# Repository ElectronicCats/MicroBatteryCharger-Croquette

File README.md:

# Electronic Cats Croquette Micro Lipo/Lion Battery Charger

This little lipo charger is so small and easy to use you can keep it on your desk or mount it easily into any project! A 3.7V/4.2V lithium polymer or lithium ion rechargeable battery into the connectors. There are two LEDs - one red and one green. While charging, the red LED is lit. When the battery is fully charged and ready for use, the green LED turns on. Seriously, it could not get more easy.

For use with LiPoly/LiIon batteries only! Other batteries may have different voltage, chemistry, polarity or pinout. Lipo/Lipoly/LiIon Batteries not included, but we've got tons in the shop.

Charging is performed in three stages: first a preconditioning charge, then a constant-current fast charge and finally a constant-voltage trickle charge to keep the battery topped-up. The charge current is 100mA by default, so it will work with any size battery and USB port. If you want you can easily change it over to 500mA mode by soldering closed the jumper on the front, for when you'll only be charging batteries with 500mAh size or larger.

- 5V input
- For charging single Lithium Ion/Lithium Polymer 3.7/4.2v batteries (not for older 3.6/4.1v cells)
- 100mA charge current, adjustable to 500mA by soldering a jumper closed

### Maintainer

Electronic Cats invests time and resources providing this open source design, please support Electronic Cats and open-source hardware by purchasing products from Electronic Cats!

### License

MIT

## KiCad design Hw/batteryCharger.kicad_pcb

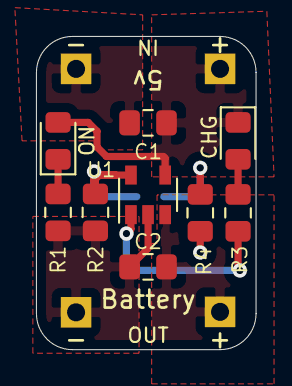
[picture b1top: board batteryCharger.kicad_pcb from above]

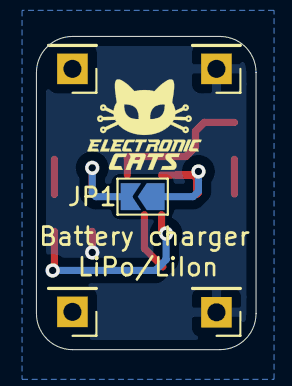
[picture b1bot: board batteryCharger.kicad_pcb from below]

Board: 2 copper layers, 12.2 x 17.4 mm, 14 parts (5 on the bottom side), 8 nets.

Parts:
C1: 10uF; C_0805_2012Metric_Pad1.15x1.40mm_HandSolder
C2: C; C_0805_2012Metric_Pad1.15x1.40mm_HandSolder
D1, D2: LED; LED_0805_2012Metric_Pad1.15x1.40mm_HandSolder
J1: Vcc; PinHeader_1x01_P2.54mm_Vertical
J2, J4: GND; PinHeader_1x01_P2.54mm_Vertical
J3: BAT; PinHeader_1x01_P2.54mm_Vertical
JP1: JP1; SolderJumper-2_P1.3mm_Open_TrianglePad1.0x1.5mm
R1: 330; R_0805_2012Metric_Pad1.15x1.40mm_HandSolder
R2: 10k; R_0805_2012Metric_Pad1.15x1.40mm_HandSolder
R3: 1k; R_0805_2012Metric_Pad1.15x1.40mm_HandSolder
R4: 2.5K; R_0805_2012Metric_Pad1.15x1.40mm_HandSolder
U1: MCP73831-2-OT; SOT-23-5

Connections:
/batt: C2.1, J3.1, U1.3
GND: C1.2, C2.2, J2.1, J4.1, R1.2, R2.1, R4.1, U1.2
unnamed: D1.1, R1.1
unnamed: D2.2, R3.2
unnamed: JP1.1, R2.2, U1.5
unnamed: JP1.2, R4.2
unnamed: R3.1, U1.1
VCC: C1.1, D1.2, D2.1, J1.1, U1.4

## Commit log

2019-07-08 Add first design
2019-07-08 Udate jumper for faster charge add logos
2019-07-22 Update schematic
2019-10-13 remove innecesary files
2022-01-07 Update_kicad_6
